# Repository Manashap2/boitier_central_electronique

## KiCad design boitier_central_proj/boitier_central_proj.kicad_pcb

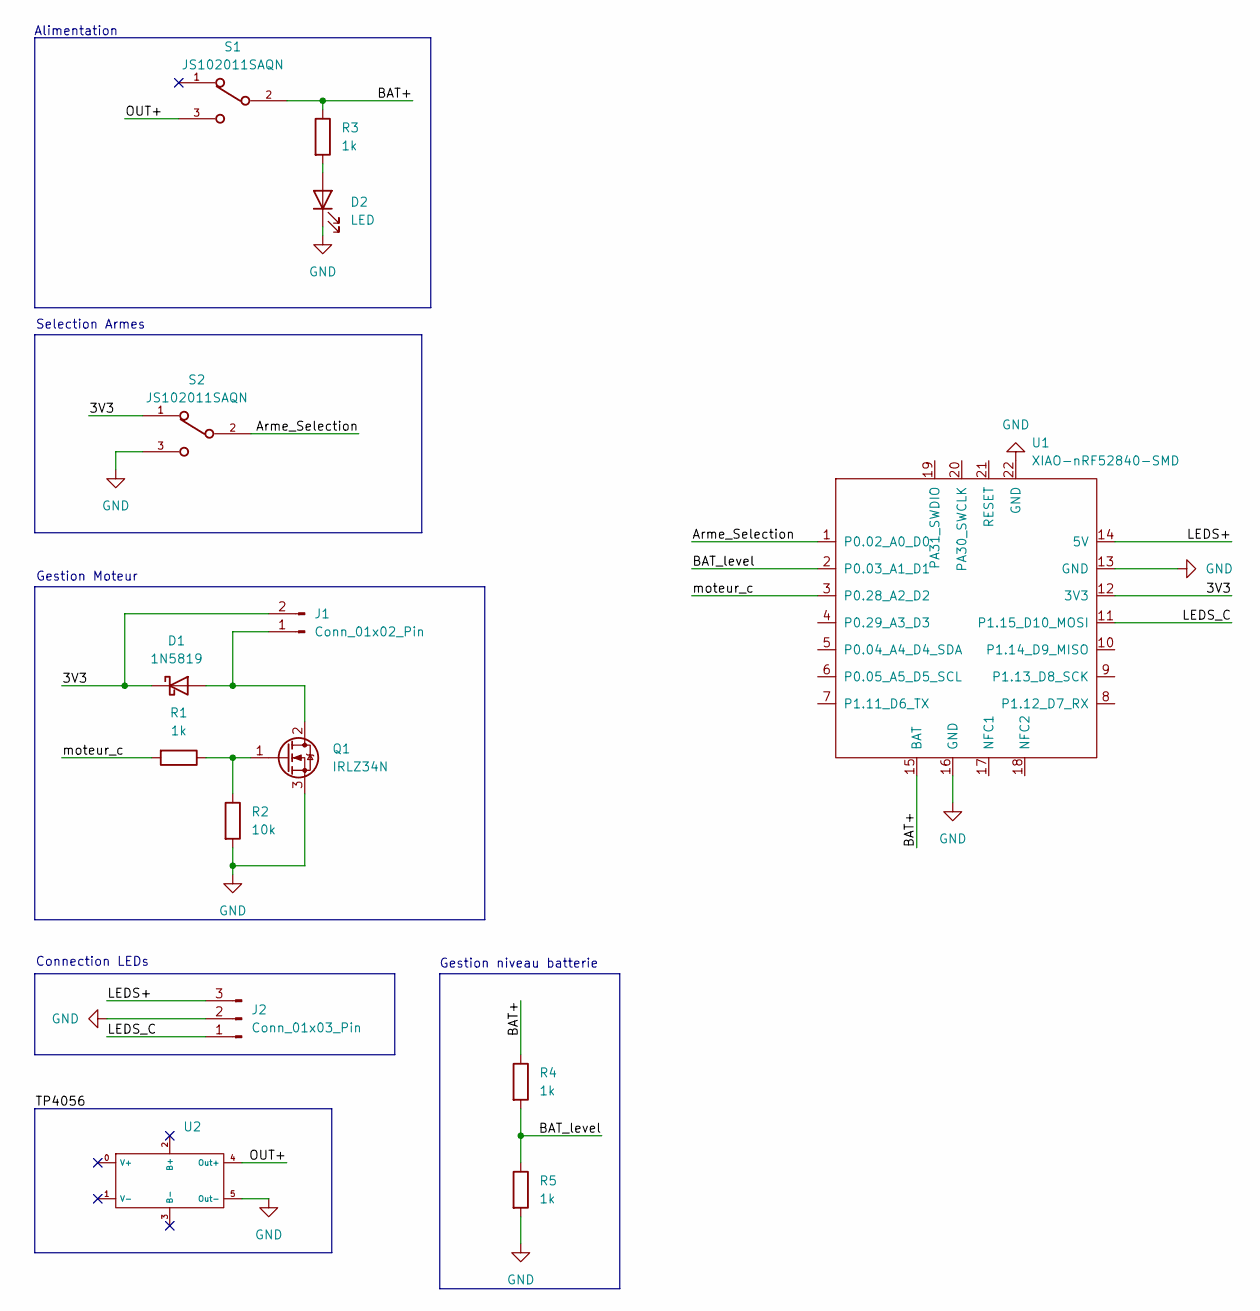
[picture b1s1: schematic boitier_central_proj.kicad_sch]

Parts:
D1: 1N5819; D_DO-41_SOD81_P10.16mm_Horizontal
D2: LED; LED_D5.0mm
J1: Conn_01x02_Pin; JST_XH_B2B-XH-A_1x02_P2.50mm_Vertical
J2: Conn_01x03_Pin; JST_XH_B3B-XH-A_1x03_P2.50mm_Vertical
Q1: IRLZ34N; TO-220-3_Vertical
R1, R3, R4, R5: 1k; R_Axial_DIN0204_L3.6mm_D1.6mm_P2.54mm_Vertical
R2: 10k; R_Axial_DIN0204_L3.6mm_D1.6mm_P2.54mm_Vertical
S1, S2: JS102011SAQN; SW_SPDT_CK_JS102011SAQN
U1: XIAO-nRF52840-SMD
U2: TP4056

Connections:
/3V3: D1.1 (K), J1.2, S2.1, U1.12 (3V3)
/Arme_Selection: S2.2, U1.1 (P0.02_A0_D0)
/BAT+: R3.1, R4.1, S1.2, U1.15 (BAT)
/BAT_level: R4.2, R5.1, U1.2 (P0.03_A1_D1)
/LEDS+: J2.3, U1.14 (5V)
/LEDS_C: J2.1, U1.11 (P1.15_D10_MOSI)
/OUT+: S1.3, U2.4 (Out+)
/moteur_c: R1.2, U1.3 (P0.28_A2_D2)
GND: D2.1 (K), J2.2, Q1.3 (S), R2.2, R5.2, S2.3, U1.13 (GND), U1.16 (GND), U1.22 (GND), U2.5 (Out-)
unnamed: D1.2 (A), J1.1, Q1.2 (D)
unnamed: D2.2 (A), R3.2
unnamed: Q1.1 (G), R1.1, R2.1

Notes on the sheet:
Gestion niveau batterie
Alimentation
Gestion Moteur
Connection LEDs
Selection Armes

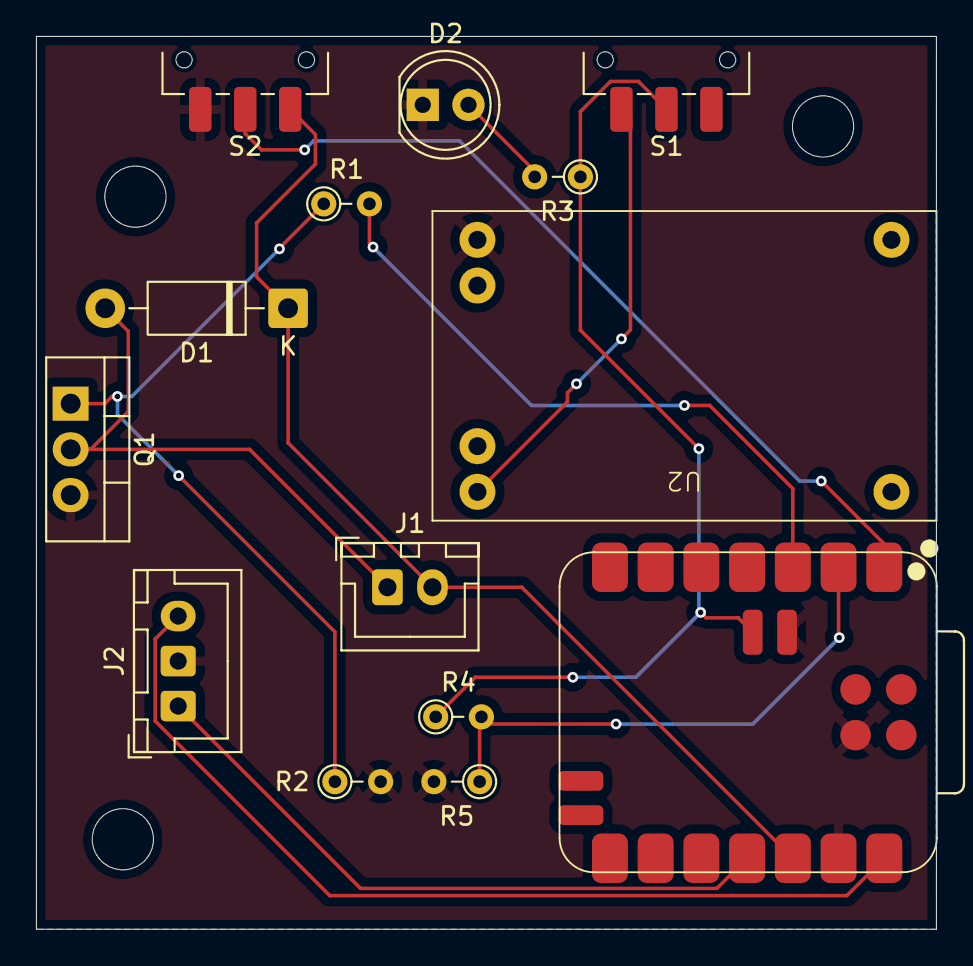
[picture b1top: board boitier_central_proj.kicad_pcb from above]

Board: 2 copper layers, 50.0 x 49.6 mm, 14 parts (0 on the bottom side), 12 nets.

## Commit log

2025-07-03 Ignore le dossier de backups KiCad
2025-07-04 PCB V1
2025-07-04 Ajout du module TP4056 dans le schematic
2025-07-07 Ajout du 3d duseeduiino et du tp4056 + ajout des trous
2025-07-07 Presque pret a etre produit
2025-07-09 Modification des trous pour le support + ajout des 3d + correction de la position du TP4056
